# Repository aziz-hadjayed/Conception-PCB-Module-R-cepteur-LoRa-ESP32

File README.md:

# Conception-PCB-Module-R-cepteur-LoRa-ESP32
Conception et routage d’un PCB récepteur LoRa à base d’ESP32-WROOM-32 et module RAK811-HF pour le contrôle de servomoteurs, avec alimentation USB‑C 3,3 V et ligne RF 50 Ω optimisée.

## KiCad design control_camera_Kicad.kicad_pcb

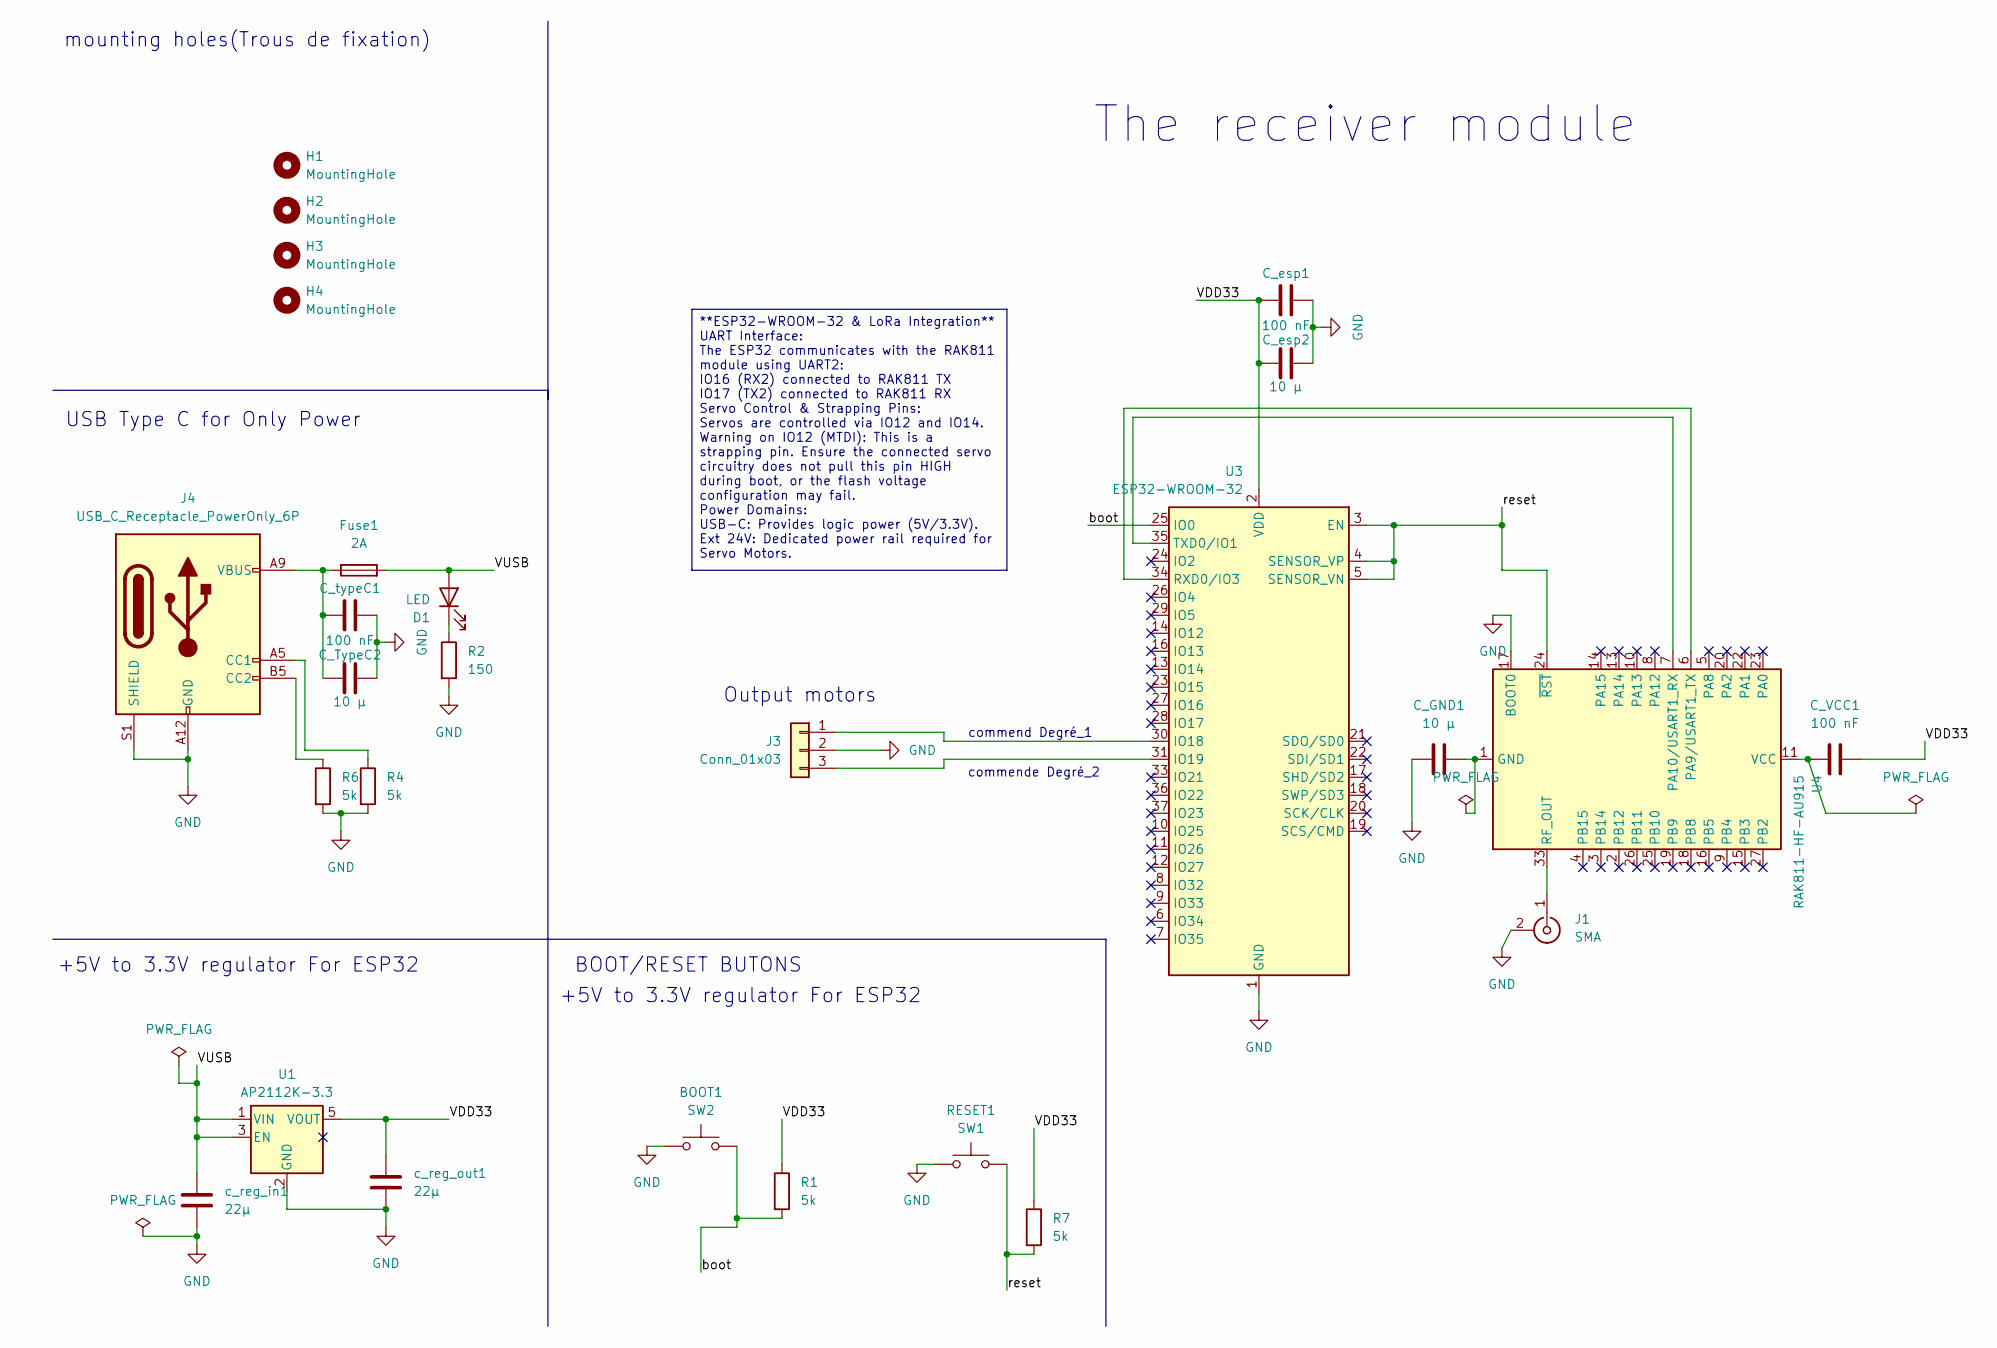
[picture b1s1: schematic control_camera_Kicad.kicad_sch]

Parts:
BOOT1: SW2; SW_PUSH_1P1T_6x3.5mm_H5.0_APEM_MJTP1250
C_GND1: 10 µ; CP_Elec_6.3x5.3
C_TypeC2: 10 µ; CP_Elec_6.3x5.3
C_VCC1: 100 nF; C_01005_0402Metric
C_esp1: 100 nF; C_01005_0402Metric
C_esp2: 10 µ; CP_Elec_6.3x5.3
C_typeC1: 100 nF; C_01005_0402Metric
D1: LED; LED_0201_0603Metric
Fuse1: 2A; Fuse_Bourns_MF-RHT200
H1, H2, H3, H4: MountingHole; MountingHole_2.1mm
J1: SMA; WR-MMCX_Wuerth_66012102111404_Vertical
J3: Conn_01x03; PinSocket_1x03_P1.00mm_Vertical
J4: USB_C_Receptacle_PowerOnly_6P; USB_C_Receptacle_GCT_USB4125-xx-x-0190_6P_TopMnt_Horizontal
R1, R4, R6, R7: 5k; R_Axial_DIN0207_L6.3mm_D2.5mm_P2.54mm_Vertical
R2: 150; R_0201_0603Metric
RESET1: SW1; SW_PUSH_1P1T_6x3.5mm_H5.0_APEM_MJTP1250
U1: AP2112K-3.3; SOT-23-5
U3: ESP32-WROOM-32
U4: RAK811-HF-AU915; RAK811
c_reg_in1: 22µ; CP_Elec_6.3x5.3
c_reg_out1: 22µ; CP_Elec_6.3x5.3

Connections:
/VDD33: C_VCC1.1, C_esp1.2, C_esp2.2, R1.1, R7.1, U1.5 (VOUT), U3.2 (VDD), c_reg_out1.1
/VUSB: D1.2 (A), Fuse1.2, U1.1 (VIN), U1.3 (EN), c_reg_in1.1
/boot: BOOT1.2, R1.2, U3.25 (IO0)
/reset: R7.2, RESET1.2, U3.3 (EN), U3.4 (SENSOR_VP), U3.5 (SENSOR_VN), U4.24 (~RST)
GND: BOOT1.1, C_GND1.2, C_TypeC2.1, C_esp1.1, C_esp2.1, C_typeC1.1, J1.2 (Ext), J3.2, J4.A12 (GND), J4.B12 (GND), J4.S1 (SHIELD), R2.2, R4.2, R6.2, RESET1.1, U1.2 (GND), U3.1 (GND), U3.15 (GND), U3.38 (GND), U3.39 (GND), U4.17 (BOOT0), c_reg_in1.2, c_reg_out1.2
unnamed: C_GND1.1, U4.1 (GND), U4.12 (GND), U4.21 (GND), U4.28 (GND), U4.29 (GND), U4.30 (GND), U4.31 (GND), U4.32 (GND), U4.34 (GND)
unnamed: C_TypeC2.2, C_typeC1.2, Fuse1.1, J4.A9 (VBUS), J4.B9 (VBUS)
unnamed: D1.1 (K), R2.1
unnamed: J1.1 (In), U4.33 (RF_OUT)
unnamed: J3.1, U3.30 (IO18)
unnamed: J3.3, U3.31 (IO19)
unnamed: J4.A5 (CC1), R4.1
unnamed: J4.B5 (CC2), R6.1
unnamed: U3.34 (RXD0/IO3), U4.6 (PA9/USART1_TX)
unnamed: U3.35 (TXD0/IO1), U4.7 (PA10/USART1_RX)
unnamed: C_VCC1.2, U4.11 (VCC)

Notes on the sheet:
+5V to 3.3V regulator For ESP32
mounting holes(Trous de fixation)
commend Degré_1
commende Degré_2
Output motors
The receiver module
USB Type C for Only Power
BOOT/RESET BUTONS
**ESP32-WROOM-32 & LoRa Integration** UART Interface: The ESP32 communicates with the RAK811 module using UART2: IO16 (RX2) connected to RAK811 TX IO17 (TX2) connected to RAK811 RX Servo Control & Strapping Pins: Servos are controlled via IO12 and IO14. Warning on IO12 (MTDI): This is a strapping p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

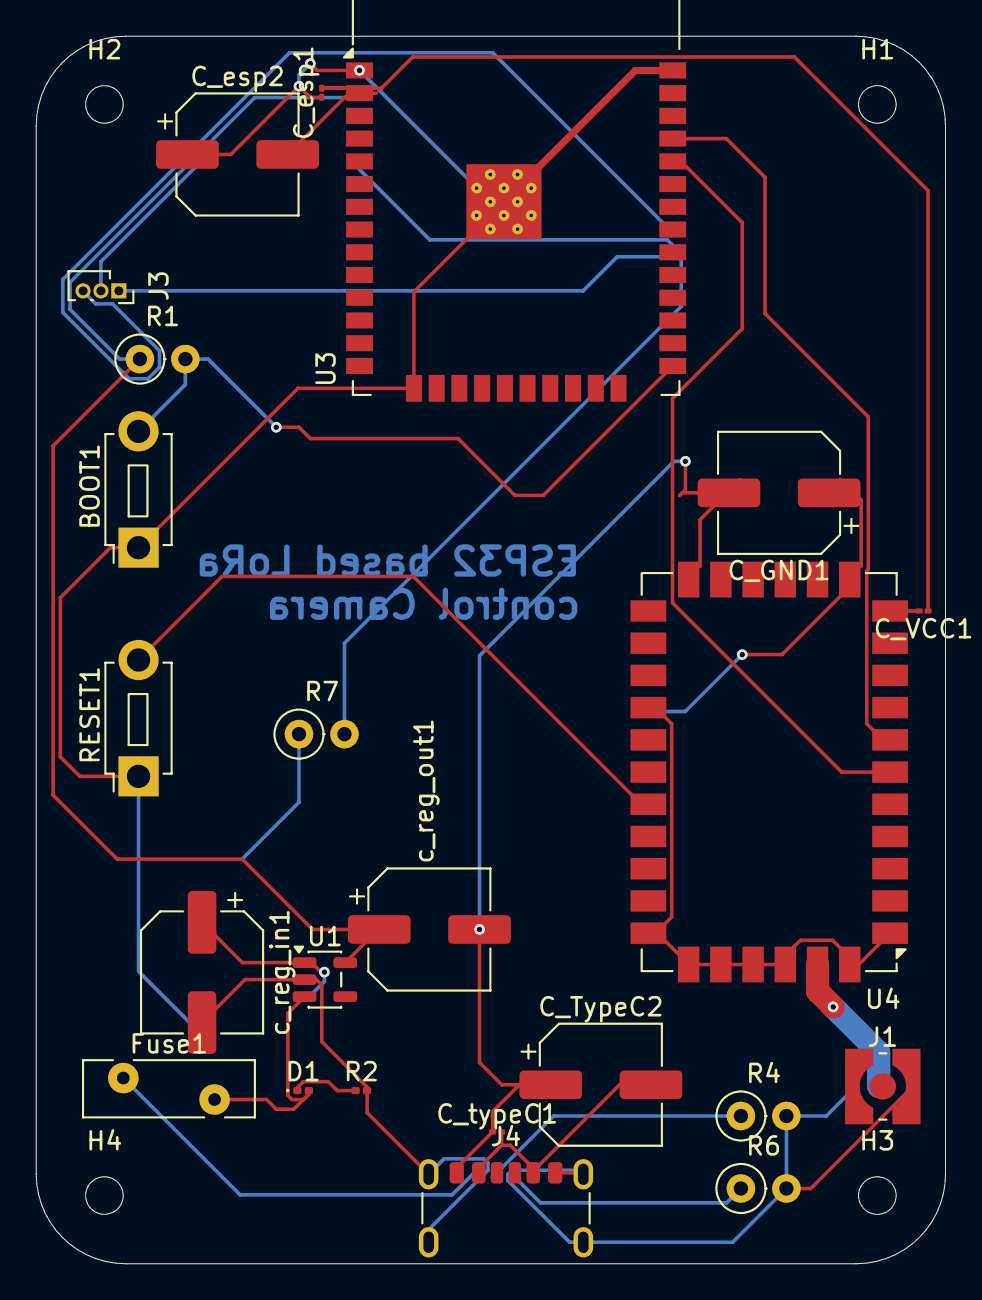
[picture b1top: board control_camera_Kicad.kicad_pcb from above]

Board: 2 copper layers, 50.8 x 68.6 mm, 27 parts (0 on the bottom side), 16 nets.
